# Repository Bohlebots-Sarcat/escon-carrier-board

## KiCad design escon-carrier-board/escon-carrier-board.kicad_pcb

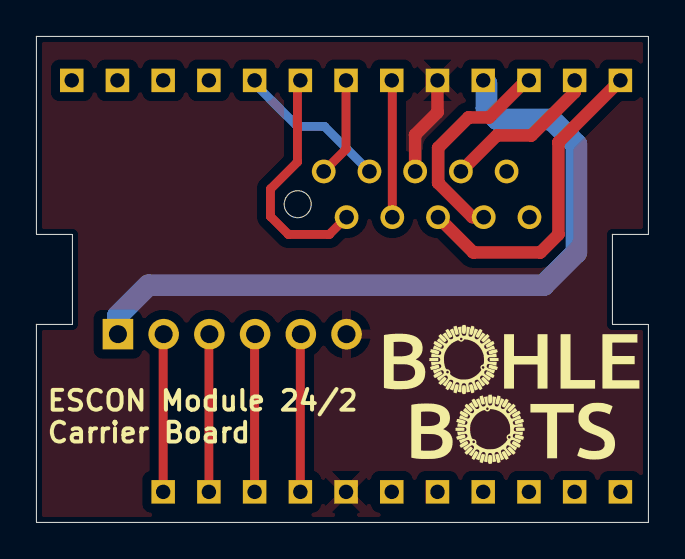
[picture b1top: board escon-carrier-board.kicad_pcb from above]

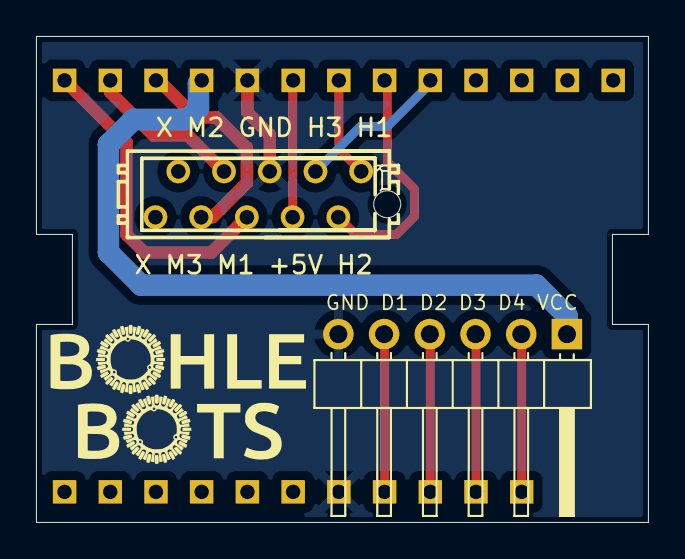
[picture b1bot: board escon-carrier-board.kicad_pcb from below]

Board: 2 copper layers, 34.0 x 27.0 mm, 3 parts (2 on the bottom side), 13 nets.

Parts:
ESCON1: 24_2; ESCOM_24_2
J1: Conn_01x06; PinHeader_1x06_P2.54mm_Horizontal
X1: MICROMATCH-10

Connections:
GND: ESCON1.P5 (GND), ESCON1.P18 (GND), J1.6, X1.5 (S)
unnamed: ESCON1.P6 (+5V), X1.4 (S)
unnamed: ESCON1.P17 (D1), J1.5
unnamed: ESCON1.P16 (D2), J1.4
unnamed: ESCON1.P15 (D3), J1.3
unnamed: ESCON1.P14 (D4), J1.2
unnamed: ESCON1.P7 (H1), X1.1 (S)
unnamed: ESCON1.P8 (H2), X1.2 (S)
unnamed: ESCON1.P9 (H3), X1.3 (S)
unnamed: ESCON1.P1 (M1), X1.6 (S)
unnamed: ESCON1.P2 (M2), X1.7 (S)
unnamed: ESCON1.P3 (M3), X1.8 (S)
unnamed: ESCON1.P4 (VCC), J1.1

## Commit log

2024-06-25 Add KiCAD Project
2024-06-25 Added .gitignore
2024-06-25 Added BohleBots Library
2024-06-25 Finished PCB
2024-06-25 Changed .gitignore
2024-06-25 V.1.0
2024-06-26 V2.0
2024-06-30 V3.0
2024-07-25 V4.0
2024-07-25 V5.0
2024-09-17 Changed to micromatch 10 pole connector
2024-09-19 Gerber Files
